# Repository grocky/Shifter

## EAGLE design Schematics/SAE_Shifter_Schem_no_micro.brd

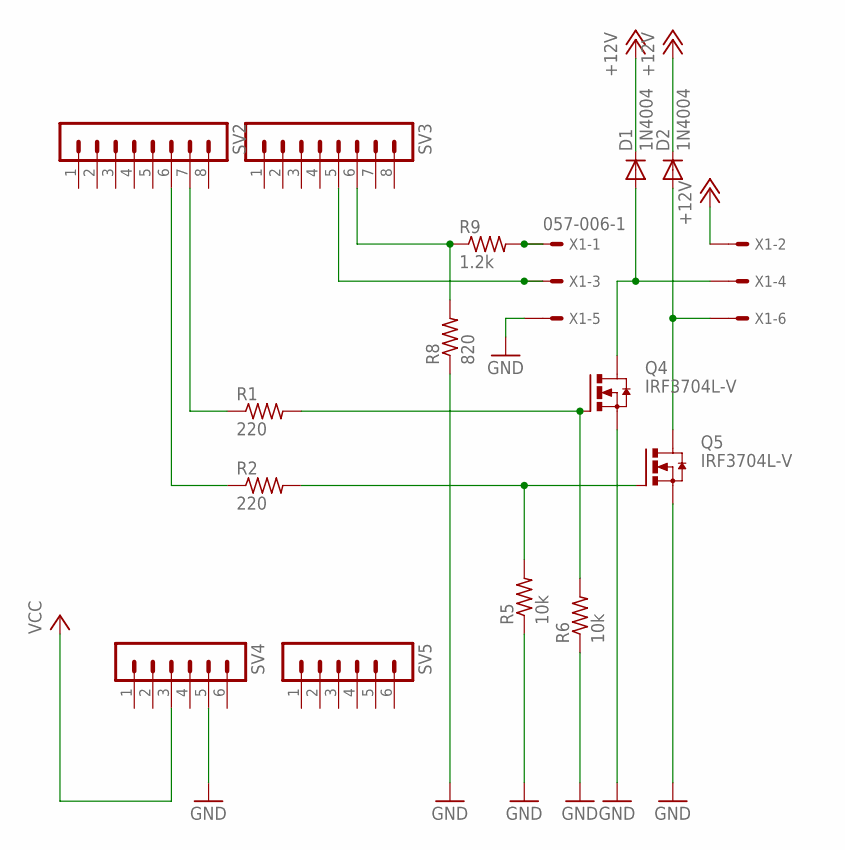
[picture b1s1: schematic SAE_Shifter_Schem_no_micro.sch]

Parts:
D1, D2: 1N4004; DO41-10
Q4, Q5: IRF3704L-V; TO262-V
R1, R2: 220; 0207/10
R5, R6: 10k; 0207/10
R8: 820; 0207/10
R9: 1.2k; 0207/10
SV2, SV3: MA08-1
SV4, SV5: MA06-1
X1: 057-006-1

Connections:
+12V: D1.C, D2.C, X1.2
GND: Q4.3 (S), Q5.3 (S), R5.1, R6.1, R8.1, SV4.5, X1.5
unnamed: D1.A, Q4.2 (D), X1.4
unnamed: D2.A, Q5.2 (D), X1.6
unnamed: R1.1, SV2.7
unnamed: R8.2, R9.1, SV3.6
unnamed: Q5.1 (G), R2.2, R5.2
unnamed: SV3.5, X1.3
unnamed: R2.1, SV2.6
unnamed: R9.2, X1.1
unnamed: Q4.1 (G), R1.2, R6.2
VCC: SV4.3

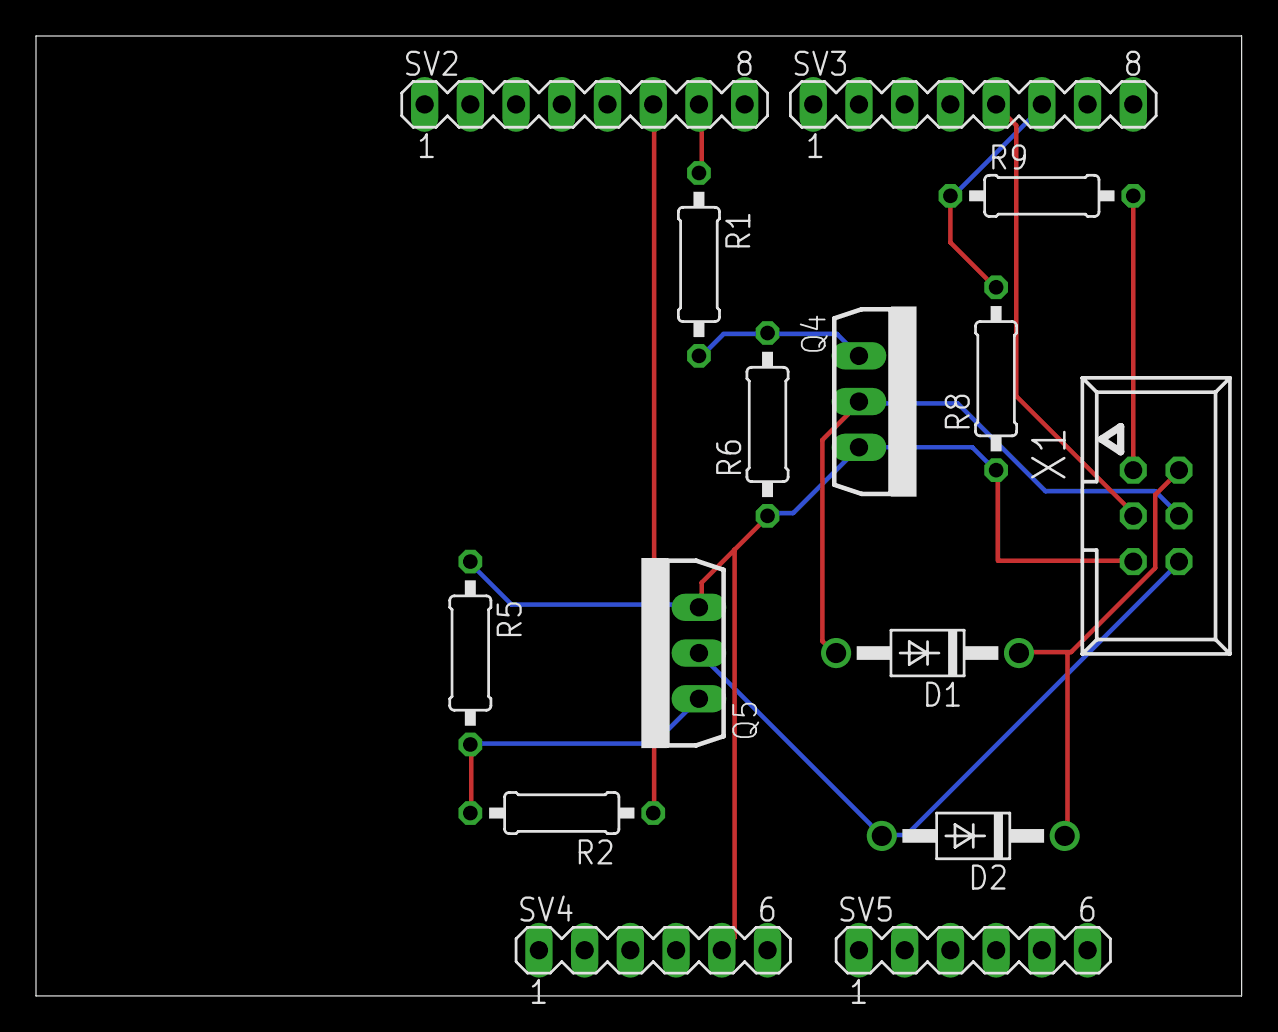
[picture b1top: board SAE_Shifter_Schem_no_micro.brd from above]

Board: 2 copper layers, 67.0 x 53.3 mm, 15 parts (0 on the bottom side), 11 nets.

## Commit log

2012-09-19 Initial commit.
2012-09-19 README added.
2012-09-19 Restructured folders and changed MAKEFILE
2012-09-19 Restructured files
2012-09-19 Added interface files
2012-09-19 Interface README
2012-09-23 Added .gitignore
    Added bin/.gitignore
    squash
    Make wrapper script
    squash
    squash
2012-09-23 Moved ISR functions to main.c Transformed inline functions in SAE_AutoShifter.h into functions in SAE_AutoShifter.c
2012-09-29 Added schematics, notes, and supporting documents
2012-09-29 updated gitignroe
